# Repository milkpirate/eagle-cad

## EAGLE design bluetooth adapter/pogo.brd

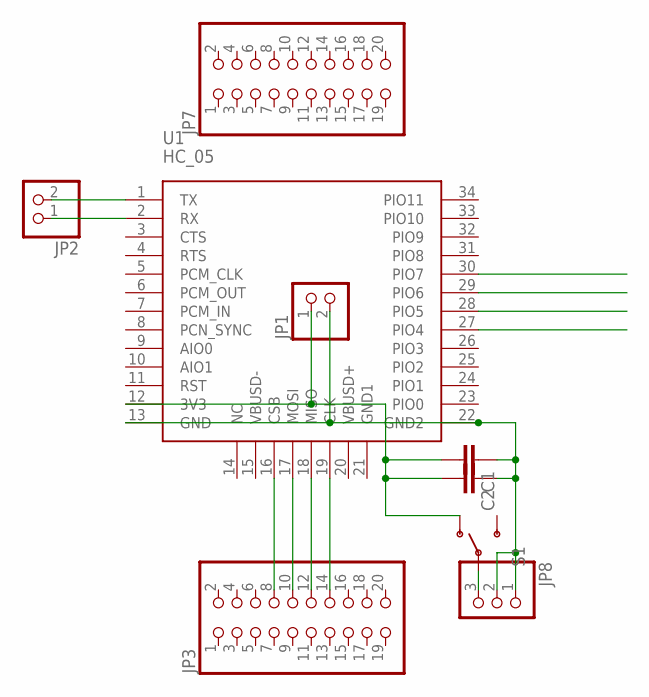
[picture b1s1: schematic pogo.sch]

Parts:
C1, C2: C-EUC0805; C0805
JP1, JP2: PINHD-1X2; 1X02
JP3, JP7: PINHD-2X10; 2X10
JP8: PINHD-1X3; 1X03
S1: SWITCH-SPDT-SMD-A; SWITCH-SPST-SMD-A
U1: HC_05; BLUETOOTH_SMD

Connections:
unnamed: JP8.3, S1.2
unnamed: C1.2, C2.2, JP1.1, S1.1 (O), U1.12 (3V3)
unnamed: C1.1, C2.1, JP1.2, JP8.1, JP8.2, U1.13 (GND), U1.22 (GND2)
unnamed: JP2.1, U1.2 (RX)
unnamed: JP2.2, U1.1 (TX)
unnamed: JP3.8, U1.16 (CSB)
unnamed: JP3.10, U1.17 (MOSI)
unnamed: JP3.12, U1.18 (MISO)
unnamed: JP3.14, U1.19 (CLK)

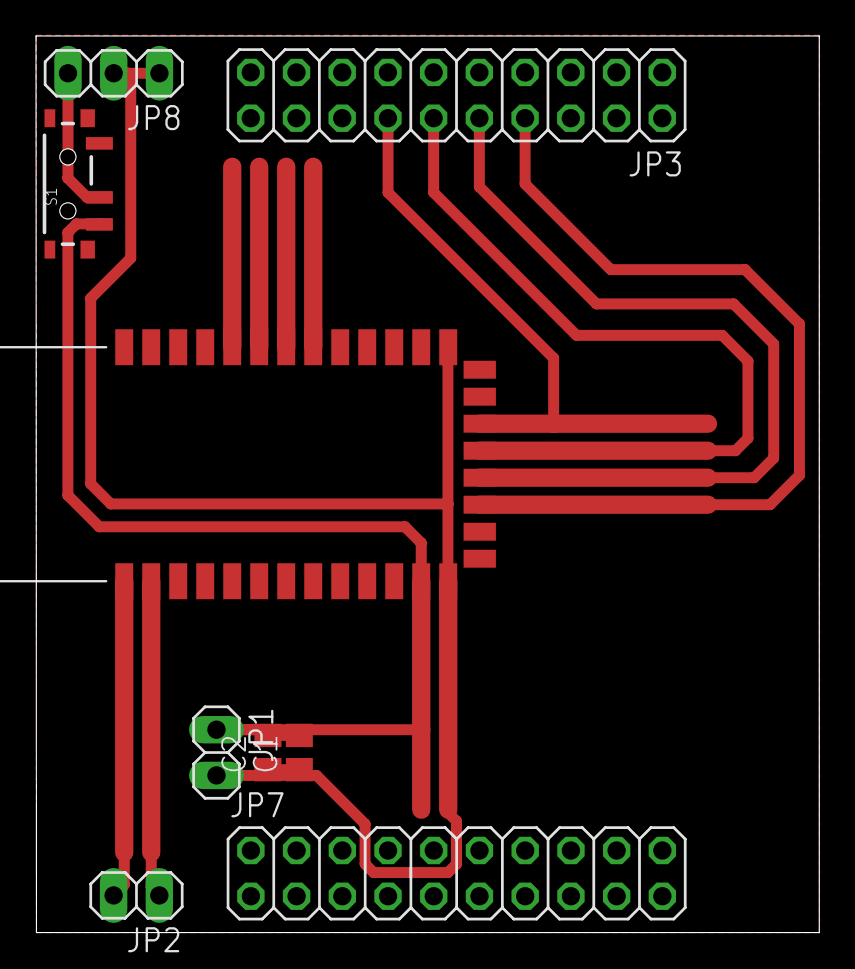
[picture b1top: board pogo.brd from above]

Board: 2 copper layers, 43.5 x 49.8 mm, 9 parts (0 on the bottom side), 9 nets.

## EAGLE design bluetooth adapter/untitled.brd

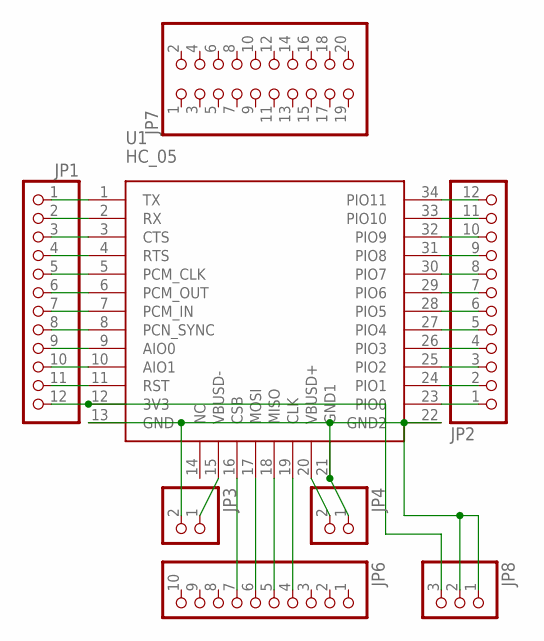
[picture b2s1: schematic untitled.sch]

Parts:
JP1, JP2: PINHD-1X12; 1X12
JP3, JP4: PINHD-1X2; 1X02
JP6: PINHD-1X10; 1X10
JP7: PINHD-2X10; 2X10
JP8: PINHD-1X3; 1X03
U1: HC_05; BLUETOOTH_SMD

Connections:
unnamed: JP1.1, U1.1 (TX)
unnamed: JP1.2, U1.2 (RX)
unnamed: JP1.3, U1.3 (CTS)
unnamed: JP1.4, U1.4 (RTS)
unnamed: JP1.5, U1.5 (PCM_CLK)
unnamed: JP1.6, U1.6 (PCM_OUT)
unnamed: JP1.7, U1.7 (PCM_IN)
unnamed: JP1.8, U1.8 (PCN_SYNC)
unnamed: JP1.9, U1.9 (AIO0)
unnamed: JP1.10, U1.10 (AIO1)
unnamed: JP1.11, U1.11 (RST)
unnamed: JP3.2, JP4.1, JP8.1, JP8.2, U1.13 (GND), U1.21 (GND1), U1.22 (GND2)
unnamed: JP2.1, U1.23 (PIO0)
unnamed: JP2.2, U1.24 (PIO1)
unnamed: JP2.3, U1.25 (PIO2)
unnamed: JP1.12, JP8.3, U1.12 (3V3)
unnamed: JP2.4, U1.26 (PIO3)
unnamed: JP2.5, U1.27 (PIO4)
unnamed: JP2.6, U1.28 (PIO5)
unnamed: JP2.7, U1.29 (PIO6)
unnamed: JP2.8, U1.30 (PIO7)
unnamed: JP2.9, U1.31 (PIO8)
unnamed: JP2.10, U1.32 (PIO9)
unnamed: JP2.11, U1.33 (PIO10)
unnamed: JP2.12, U1.34 (PIO11)
unnamed: JP3.1, U1.15 (VBUSD-)
unnamed: JP6.7, U1.16 (CSB)
unnamed: JP6.6, U1.17 (MOSI)
unnamed: JP6.5, U1.18 (MISO)
unnamed: JP6.4, U1.19 (CLK)
unnamed: JP4.2, U1.20 (VBUSD+)

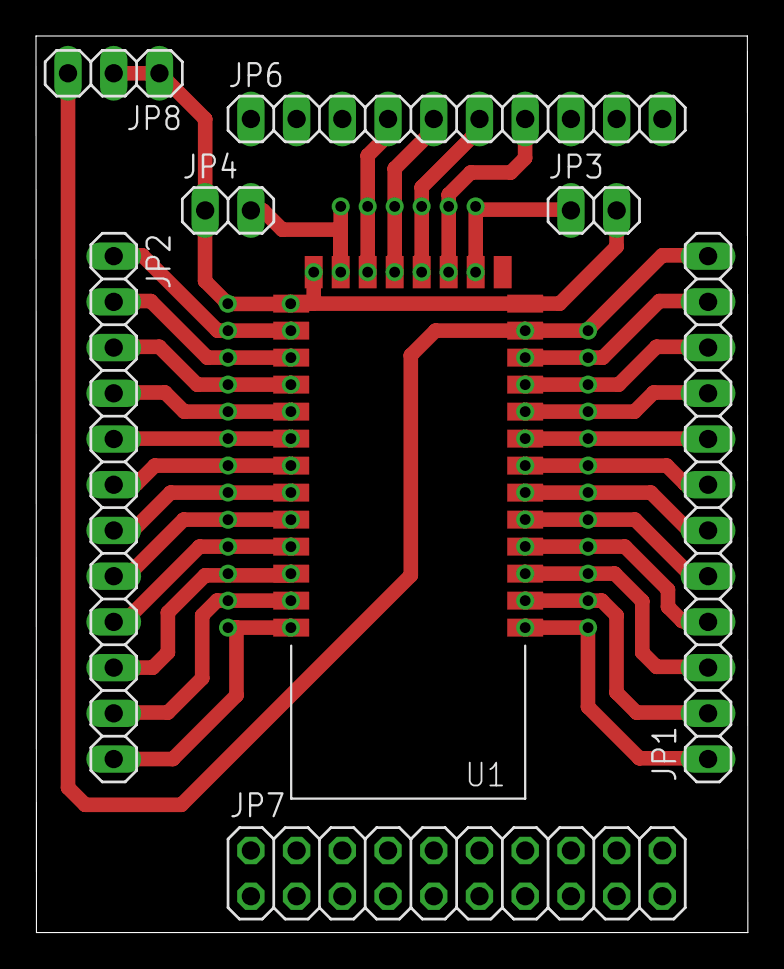
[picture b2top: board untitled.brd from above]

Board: 2 copper layers, 39.5 x 49.8 mm, 8 parts (0 on the bottom side), 31 nets.

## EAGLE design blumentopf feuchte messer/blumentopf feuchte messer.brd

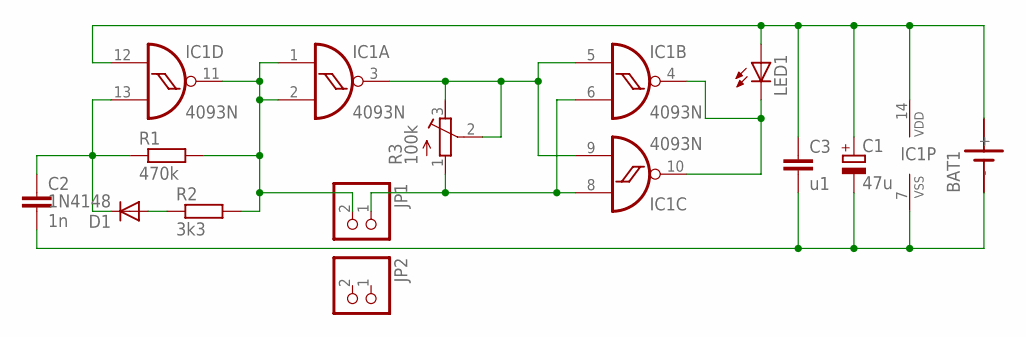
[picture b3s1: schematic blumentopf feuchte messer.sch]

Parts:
BAT1: SN2032
C1: 47u; E2,5-5
C2: 1n; C025-025X050
C3: u1; C025-025X050
D1: 1N4148; D-2.5
IC1: 4093N; DIL14
JP1, JP2: PINHD-1X2; 1X02
LED1: LED3MM
R1: 470k; 0207/2V
R2: 3k3; 0207/2V
R3: 100k; RTRIM64X

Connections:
A: IC1.6 (I1), IC1.8 (I0), JP1.1, R3.1 (A)
B: IC1.1 (I0), IC1.2 (I1), IC1.11 (O), JP1.2, R1.2, R2.2
GND: BAT1.-, C1.-, C2.2, C3.2, IC1.7 (VSS)
unnamed: BAT1.+, C1.+, C3.1, IC1.12 (I0), IC1.14 (VDD), LED1.A
unnamed: IC1.4 (O), IC1.10 (O), LED1.K (C)
unnamed: IC1.3 (O), IC1.5 (I0), IC1.9 (I1), R3.2 (S), R3.3 (E)
unnamed: C2.1, D1.C, IC1.13 (I1), R1.1
unnamed: D1.A, R2.1

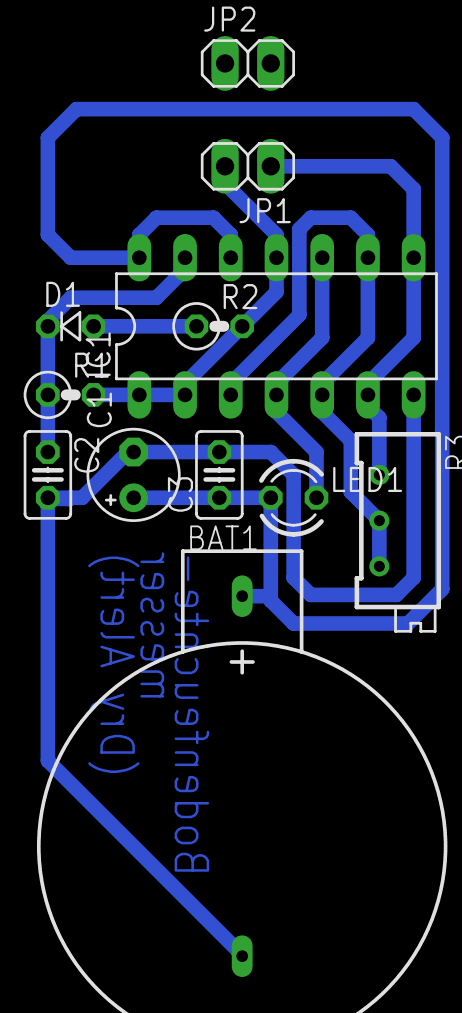
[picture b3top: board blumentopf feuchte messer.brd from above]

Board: 2 copper layers, 12 parts (0 on the bottom side), 8 nets.

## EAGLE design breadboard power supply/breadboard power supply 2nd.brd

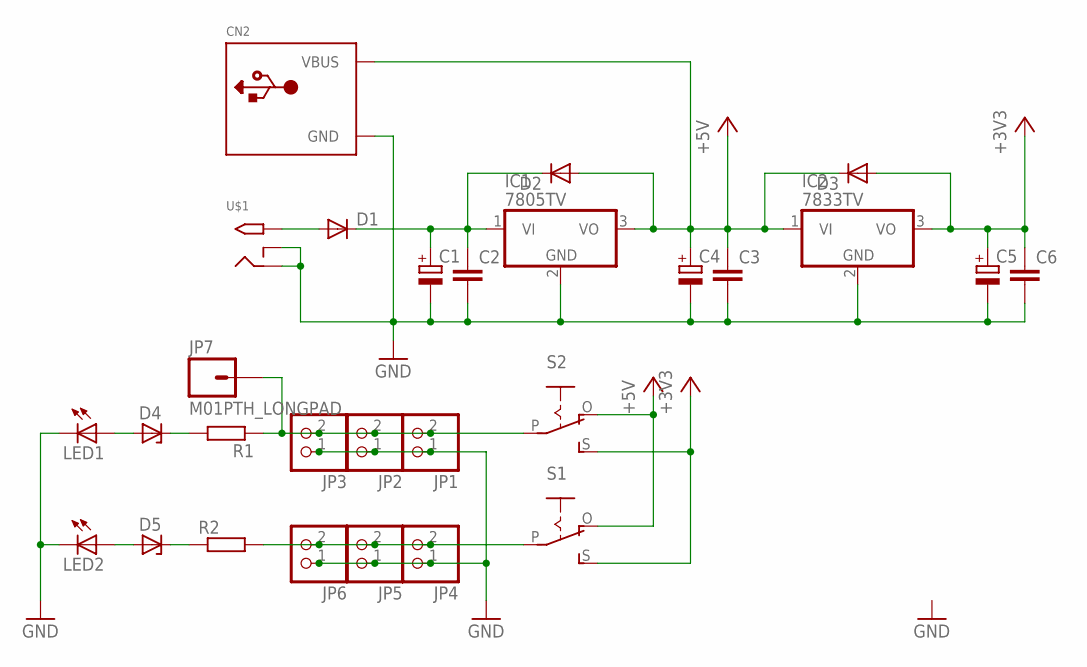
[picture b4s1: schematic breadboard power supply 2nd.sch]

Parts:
C1, C4, C5: CPOL-EUE2.5-6; E2,5-6
C2, C3, C6: C-EU025-025X050; C025-025X050
CN2: USB; USB-MINIB-THM
D1, D2, D3: DIODE-D-5; D-5
D4, D5: ZENER-DIODEZD-2.5; ZDIO-2.5
IC1: 7805TV; TO220V
IC2: 7833TV; TO220V
JP1, JP2, JP3, JP4, JP5, JP6: PINHD-1X2; 1X02
JP7: M01PTH_LONGPAD; 1X01_LONGPAD
LED1, LED2: LED3MM
R1, R2: R-EU_0204/2V; 0204V
S1, S2: EG1218S; EG1218
U$1: 2.1MMJACKTHM; PJ-102A

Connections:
+3V3: C5.+, C6.1, D3.A, IC2.3 (VO), S1.S, S2.S
+5V: C3.1, C4.+, CN2.VBUS, D2.A, D3.C, IC1.3 (VO), IC2.1 (VI), S1.O, S2.O
GND: C1.-, C2.2, C3.2, C4.-, C5.-, C6.2, CN2.GND, IC1.2 (GND), IC2.2 (GND), JP1.1, JP2.1, JP3.1, JP4.1, JP5.1, JP6.1, LED1.K (C), LED2.K (C), U$1.RING, U$1.RING_SW
unnamed: D1.A, U$1.TIP
unnamed: D5.C, R2.1
unnamed: C1.+, C2.1, D1.C, D2.C, IC1.1 (VI)
unnamed: JP1.2, JP2.2, JP3.2, JP7.1, R1.1, S2.P
unnamed: D4.C, R1.2
unnamed: JP4.2, JP5.2, JP6.2, R2.2, S1.P
unnamed: D4.A, LED1.A
unnamed: D5.A, LED2.A

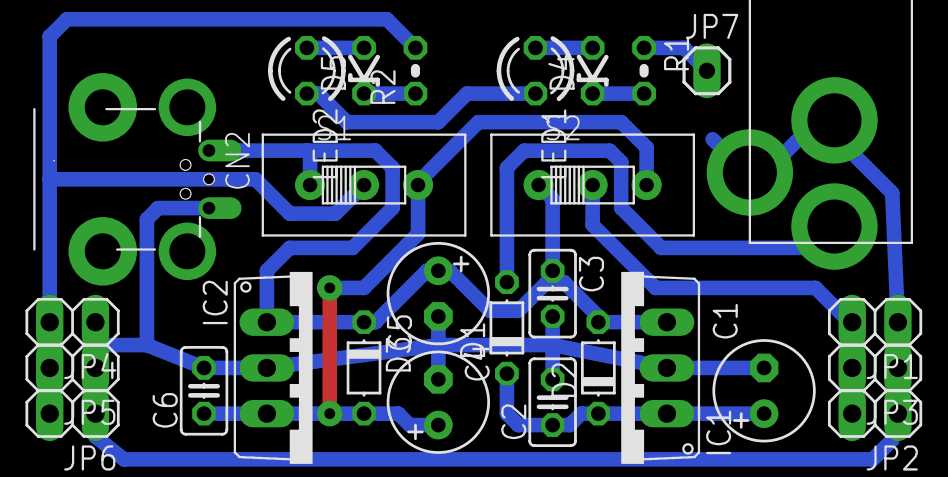
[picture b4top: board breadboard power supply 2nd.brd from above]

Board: 2 copper layers, 28 parts (0 on the bottom side), 11 nets.

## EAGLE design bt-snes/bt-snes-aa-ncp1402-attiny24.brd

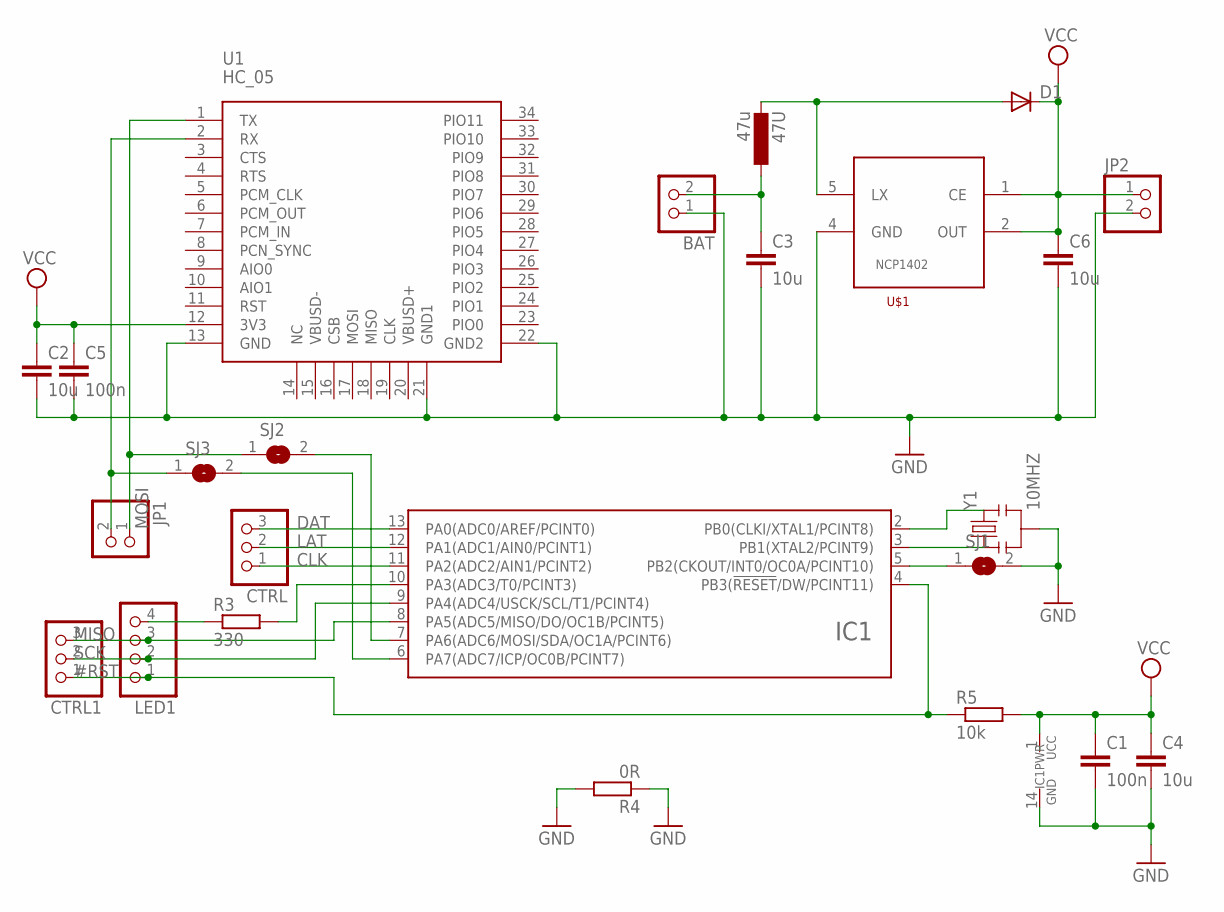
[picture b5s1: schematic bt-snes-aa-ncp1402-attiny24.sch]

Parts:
47U: 47u; C1210
BAT: PINHD-1X2; 1X02
C1, C5: 100n; C0805K
C2, C3, C4: 10u; C0805K
C6: 10u; C1206
CTRL, CTRL1: PINHD-1X3; 1X03
D1: DIODE-SOD80C; SOD80C
IC1: ATTINY24/44/84-SSU; SOIC14
JP1, JP2: PINHD-1X2; 1X02
LED1: PINHD-1X4; 1X04
R3: 330; M0805
R4: 0R; R1206W
R5: 10k; M0805
SJ1, SJ2, SJ3: SJ
U1: HC_05; BLUETOOTH_SMD
U$1: NCP1402-SOT23-5; SOT23-5
Y1: 10MHZ; RESONATOR-SMD

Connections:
#RST: CTRL1.1, IC1.4 (PB3(!RESET!/DW/PCINT11)), LED1.1, R5.1
CLK: CTRL.1, IC1.11 (PA2(ADC2/AIN1/PCINT2))
DAT: CTRL.3, IC1.13 (PA0(ADC0/AREF/PCINT0))
GND: BAT.1, C1.2, C2.2, C3.2, C4.2, C5.2, C6.2, IC1.14 (GND), JP2.2, R4.1, R4.2, SJ1.2, U1.13 (GND), U1.21 (GND1), U1.22 (GND2), U$1.4 (GND), Y1.2
LAT: CTRL.2, IC1.12 (PA1(ADC1/AIN0/PCINT1))
MISO: CTRL1.3, IC1.8 (PA5(ADC5/MISO/DO/OC1B/PCINT5)), LED1.3
MOSI: IC1.7 (PA6(ADC6/MOSI/SDA/OC1A/PCINT6)), SJ2.2
unnamed: IC1.3 (PB1(XTAL2/PCINT9)), Y1.1
unnamed: IC1.2 (PB0(CLKI/XTAL1/PCINT8)), Y1.3
unnamed: JP1.1, SJ2.1, U1.1 (TX)
unnamed: JP1.2, SJ3.1, U1.2 (RX)
unnamed: IC1.6 (PA7(ADC7/ICP/OC0B/PCINT7)), SJ3.2
unnamed: IC1.5 (PB2(CKOUT/INT0/OC0A/PCINT10)), SJ1.1
unnamed: 47U.1, BAT.2, C3.1
unnamed: 47U.2, D1.A, U$1.5 (LX)
unnamed: LED1.4, R3.1
unnamed: IC1.10 (PA3(ADC3/T0/PCINT3)), R3.2
SCK: CTRL1.2, IC1.9 (PA4(ADC4/USCK/SCL/T1/PCINT4)), LED1.2
VCC: C1.1, C2.1, C4.1, C5.1, C6.1, D1.C, IC1.1 (UCC), JP2.1, R5.2, U1.12 (3V3), U$1.1 (CE), U$1.2 (OUT)

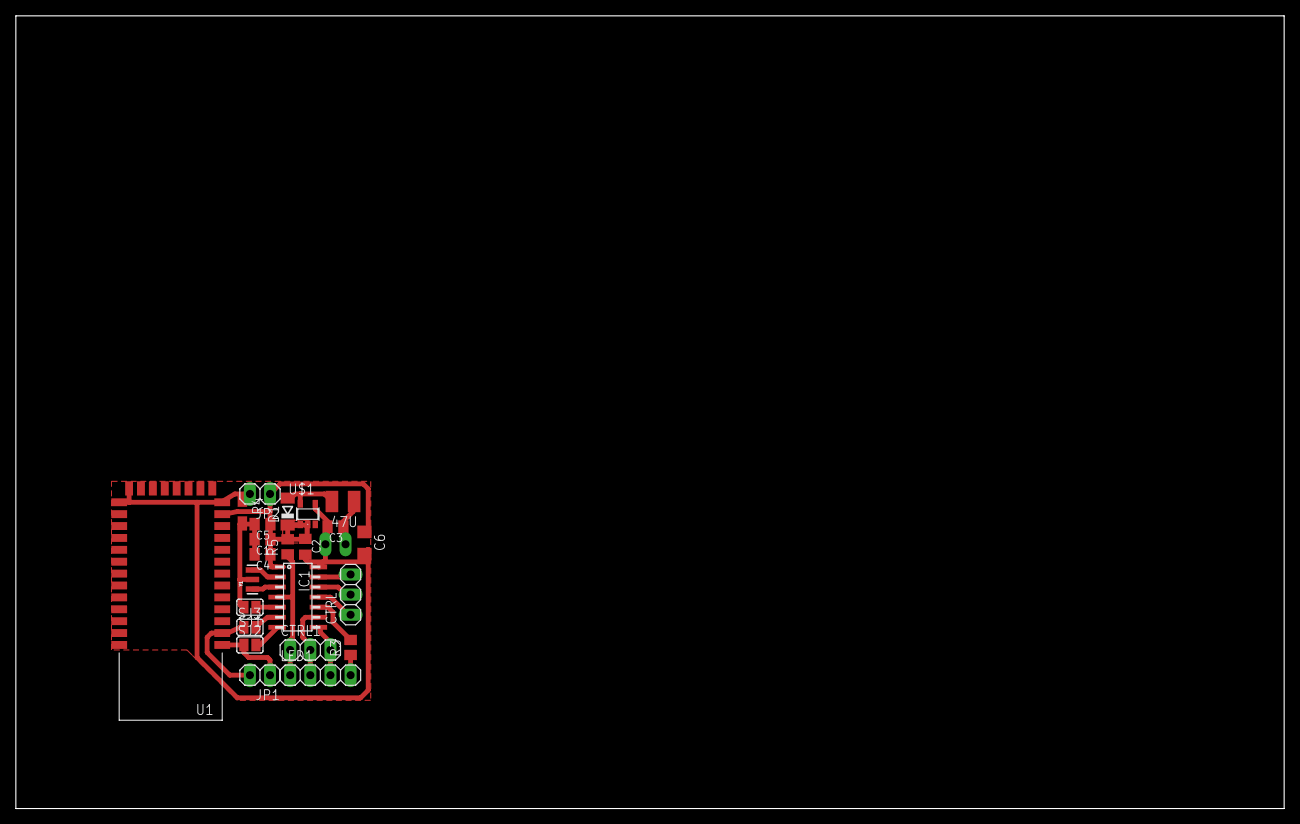
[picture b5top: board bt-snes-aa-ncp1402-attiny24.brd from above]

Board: 2 copper layers, 160.0 x 100.0 mm, 24 parts (1 on the bottom side), 19 nets.

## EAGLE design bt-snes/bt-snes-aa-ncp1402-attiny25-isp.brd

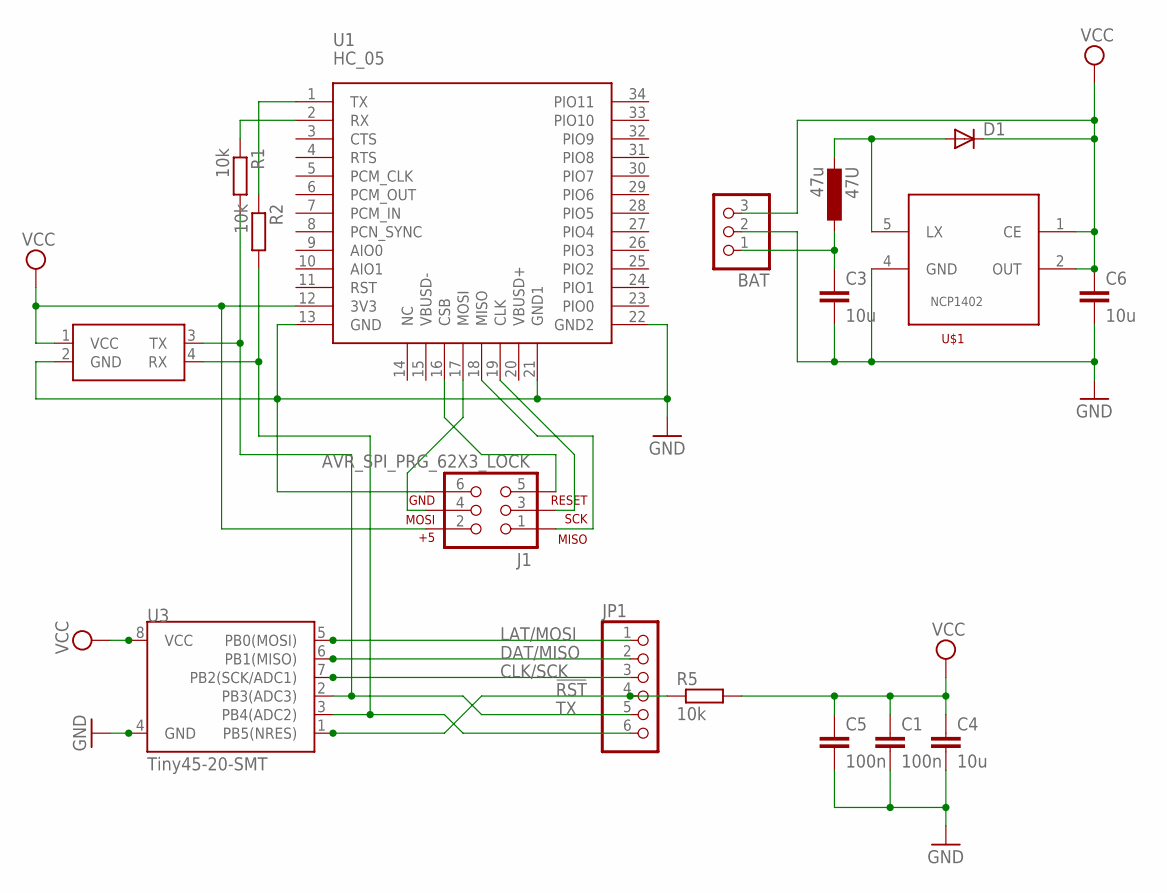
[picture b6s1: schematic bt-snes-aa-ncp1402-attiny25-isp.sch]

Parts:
47U: 47u; C1210
BAT: PINHD-1X3; 1X03
C1, C5: 100n; C0805K
C3, C4, C6: 10u; C0805K
D1: DIODE-SOD80C; SOD80C
J1: AVR_SPI_PRG_62X3_LOCK; 2X3_LOCK
JP1: PINHD-1X6; 1X06
R1, R2, R5: 10k; M0805
U1: HC_05; BLUETOOTH_SMD
U3: Tiny45-20-SMT; SO08-EIAJ
U$1: NCP1402-SOT23-5; SOT23-5
U$2: UART_CONN; UART_CONN_LOCK

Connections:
!RST: JP1.4, R5.1, U3.1 (PB5(NRES))
CLK/SCK: JP1.3, U3.7 (PB2(SCK/ADC1))
DAT/MISO: JP1.2, U3.6 (PB1(MISO))
GND: BAT.2, C1.2, C3.2, C4.2, C5.2, C6.2, J1.6, U1.13 (GND), U1.21 (GND1), U1.22 (GND2), U3.4 (GND), U$1.4 (GND), U$2.2 (GND)
LAT/MOSI: JP1.1, U3.5 (PB0(MOSI))
unnamed: JP1.6, R2.2, U3.3 (PB4(ADC2)), U$2.4 (RX)
unnamed: R1.1, U1.2 (RX)
unnamed: R2.1, U1.1 (TX)
unnamed: J1.4, U1.17 (MOSI)
unnamed: J1.5, U1.16 (CSB)
unnamed: J1.3, U1.19 (CLK)
unnamed: J1.1, U1.18 (MISO)
unnamed: 47U.1, BAT.1, C3.1
unnamed: 47U.2, D1.A, U$1.5 (LX)
TX: JP1.5, R1.2, U3.2 (PB3(ADC3)), U$2.3 (TX)
VCC: BAT.3, C1.1, C4.1, C5.1, C6.1, D1.C, J1.2, R5.2, U1.12 (3V3), U3.8 (VCC), U$1.1 (CE), U$1.2 (OUT), U$2.1 (VCC)

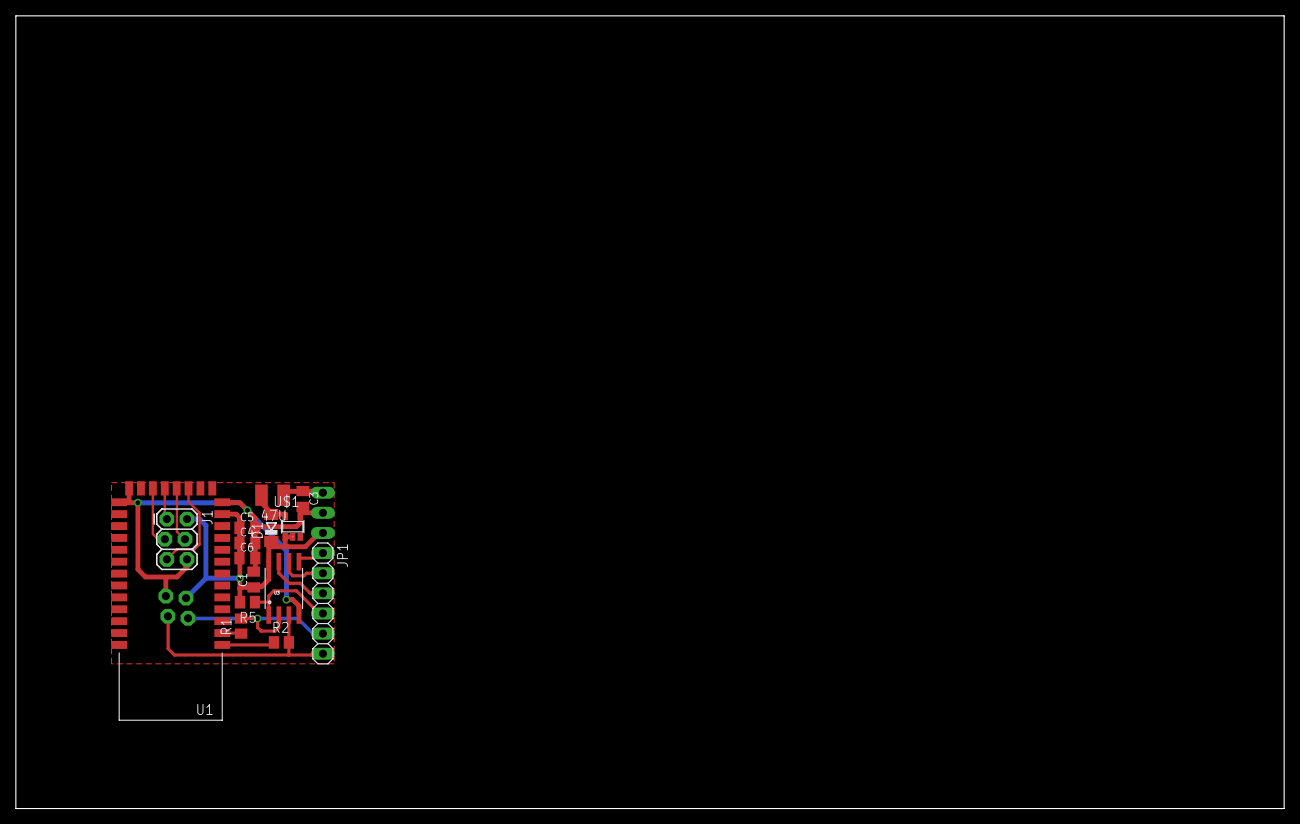
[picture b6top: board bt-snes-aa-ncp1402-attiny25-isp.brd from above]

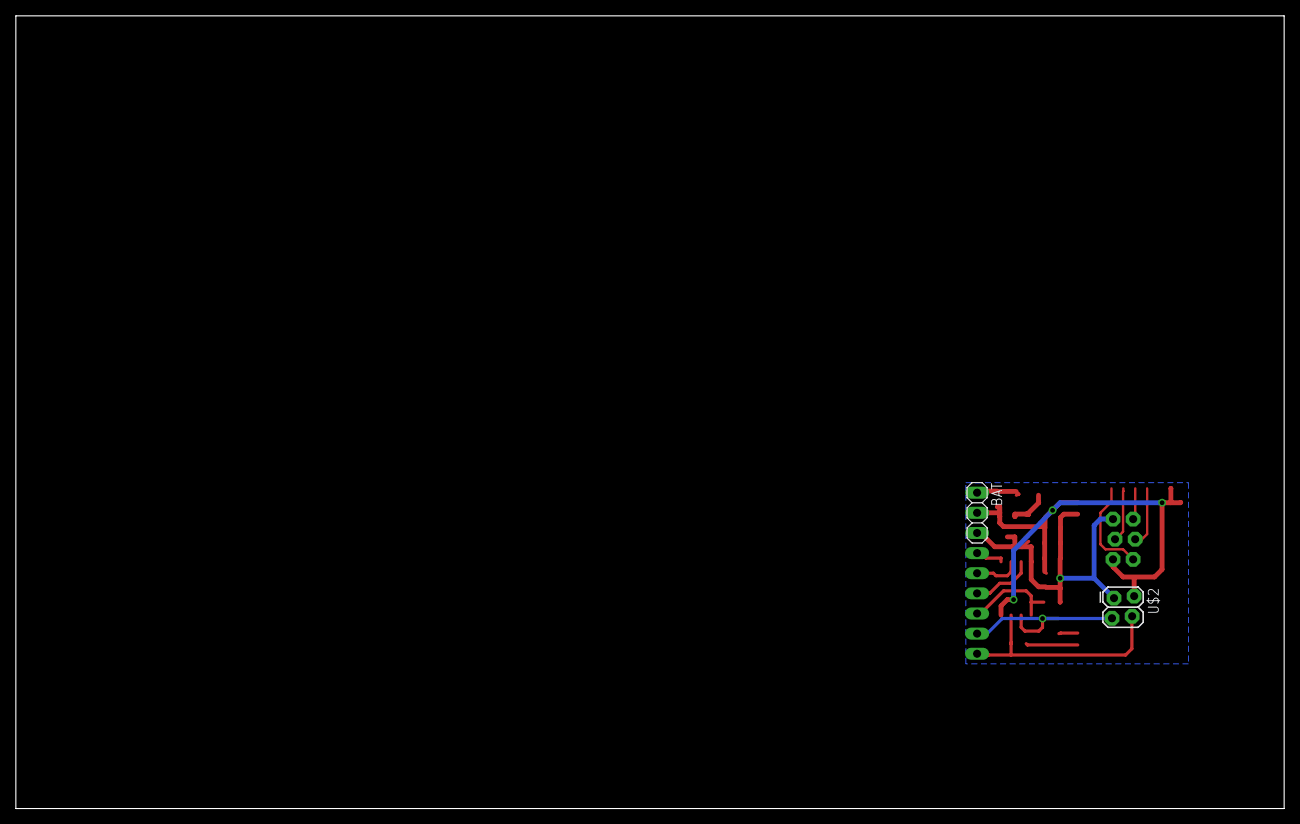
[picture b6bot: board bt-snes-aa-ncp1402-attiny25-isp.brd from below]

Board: 2 copper layers, 160.0 x 100.0 mm, 17 parts (2 on the bottom side), 16 nets.

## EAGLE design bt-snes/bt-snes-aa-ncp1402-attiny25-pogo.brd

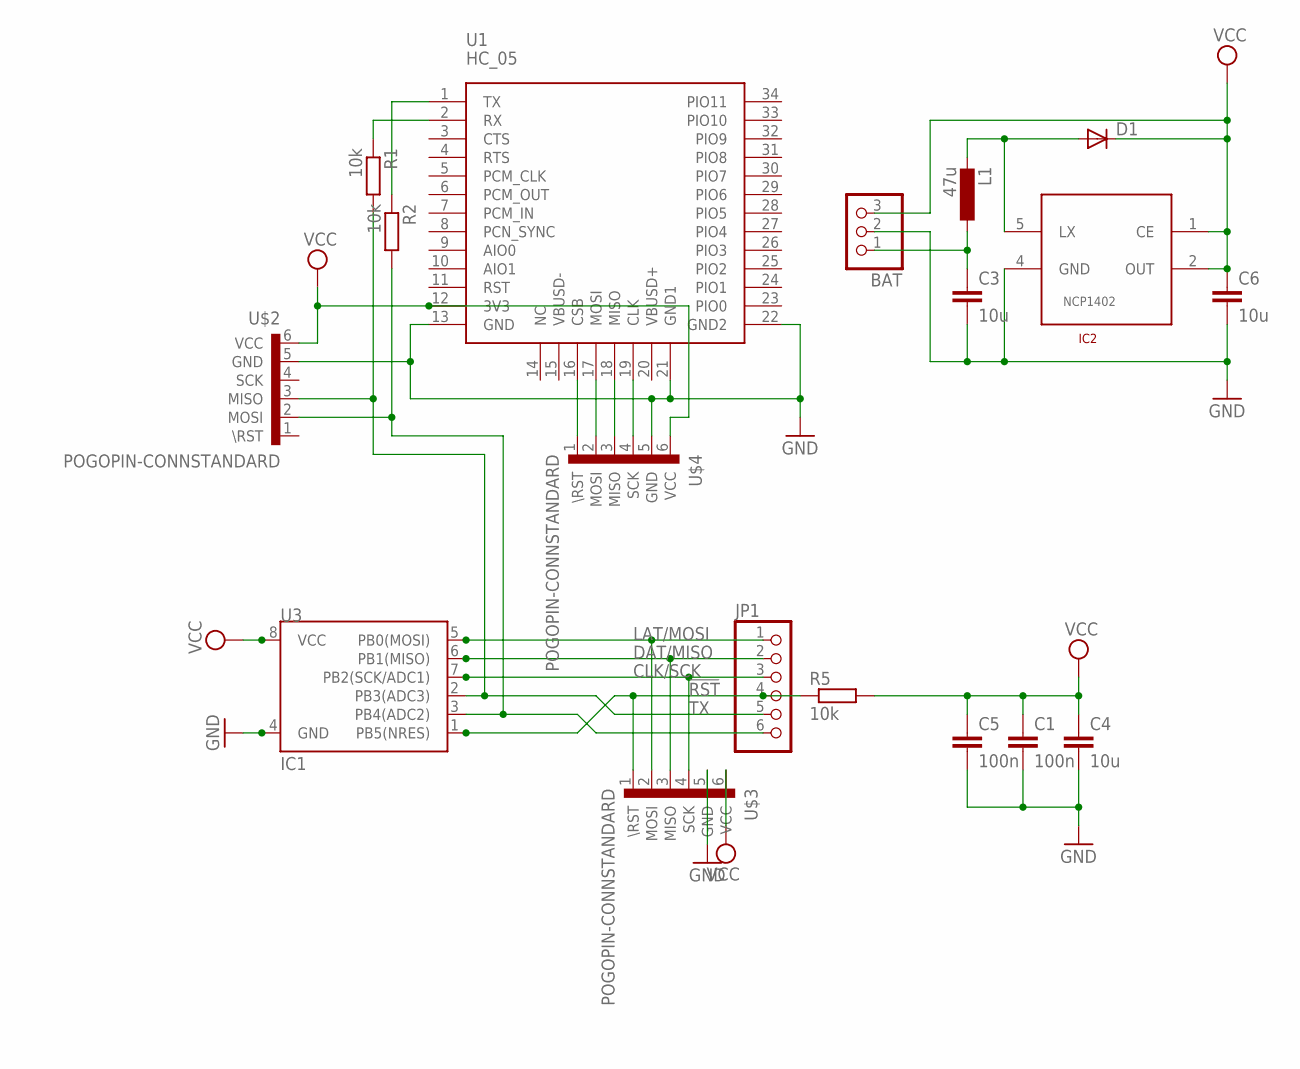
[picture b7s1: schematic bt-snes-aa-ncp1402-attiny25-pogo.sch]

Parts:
BAT: PINHD-1X3; 1X03
C1, C5: 100n; C0805K
C3, C4, C6: 10u; C0805K
D1: DIODE-SOD80C; SOD80C
IC2: NCP1402-SOT23-5; SOT23-5
JP1: PINHD-1X6; 1X06
L1: 47u; C1210
R1, R2, R5: 10k; M0805
U1: HC_05; BLUETOOTH_SMD
U3: IC1; SO08-EIAJ
U$2, U$3, U$4: POGOPIN-CONNSTANDARD; POGOPROG-CONN

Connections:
!RST: JP1.4, R5.1, U3.1 (PB5(NRES)), U$3.1 (\RST)
CLK/SCK: JP1.3, U3.7 (PB2(SCK/ADC1)), U$3.4 (SCK)
DAT/MISO: JP1.2, U3.6 (PB1(MISO)), U$3.3 (MISO)
GND: BAT.2, C1.2, C3.2, C4.2, C5.2, C6.2, IC2.4 (GND), U1.13 (GND), U1.21 (GND1), U1.22 (GND2), U3.4 (GND), U$2.5 (GND), U$3.5 (GND), U$4.5 (GND)
LAT/MOSI: JP1.1, U3.5 (PB0(MOSI)), U$3.2 (MOSI)
unnamed: JP1.6, R2.2, U3.3 (PB4(ADC2)), U$2.2 (MOSI)
unnamed: R1.1, U1.2 (RX)
unnamed: R2.1, U1.1 (TX)
unnamed: U1.17 (MOSI), U$4.2 (MOSI)
unnamed: U1.16 (CSB), U$4.1 (\RST)
unnamed: U1.19 (CLK), U$4.4 (SCK)
unnamed: U1.18 (MISO), U$4.3 (MISO)
unnamed: BAT.1, C3.1, L1.1
unnamed: D1.A, IC2.5 (LX), L1.2
TX: JP1.5, R1.2, U3.2 (PB3(ADC3)), U$2.3 (MISO)
VCC: BAT.3, C1.1, C4.1, C5.1, C6.1, D1.C, IC2.1 (CE), IC2.2 (OUT), R5.2, U1.12 (3V3), U3.8 (VCC), U$2.6 (VCC), U$3.6 (VCC), U$4.6 (VCC)

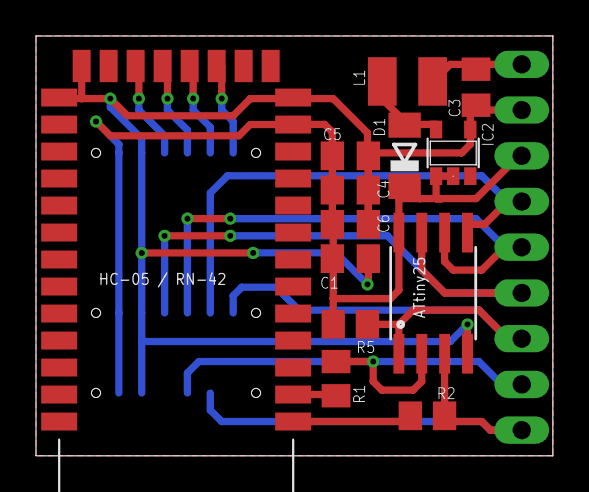
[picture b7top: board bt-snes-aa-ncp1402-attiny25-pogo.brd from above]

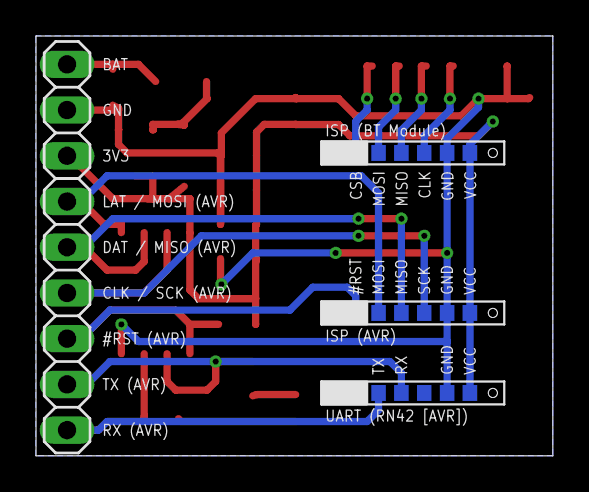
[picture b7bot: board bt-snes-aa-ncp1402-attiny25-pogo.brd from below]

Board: 2 copper layers, 28.7 x 23.3 mm, 18 parts (5 on the bottom side), 16 nets.

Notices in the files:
parts and their libraries:
SparkFun-Electromechanical: Licensing: Creative Commons ShareAlike 4.0 International - https://creativecommons.org/licenses/by-sa/4.0
SparkFun-FreqCtrl: Licensing: CC v3.0 Share-Alike You are welcome to use this library for commercial purposes.
